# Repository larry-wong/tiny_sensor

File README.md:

基于 ESP32 的家庭智能传感器，搭配 [Home Assistant](https://www.home-assistant.io/) 项目实现家自动化。

小巧的身材上集成温湿度 / 光照度 / 人体存在传感器和红外发射管。

## 硬件设计
* 主控选用 ESP32-S3-WROOM-1
* 温湿度传感器选用 HDC1080
* 光照度传感器选用 GY-302 模块
* 人体存在传感器选用 LD2410B 模块
* 红外发射选用 3mm 发射管
* 状态灯选用贴片发光二极管
* 采用 typec 口供电 / 烧写程序，针脚对应关系：

    | typec | esp32 | 备注 |
    |---|---|---|
    | GND (A1, A12, B1, B12) | GND | 接地 |
    | VBUS (A4, A9, B4, B9) | | 5V |
    | CC1 (A5), CC2 (B5) | GPIO0 | 烧写固件时需接地 |
    | D+ (A6, B6) | GPIO43 | TX |
    | D- (A7, B7) | GPIO44 | RX |

## 电路设计
原理图及 PCB 使用 kicad 绘制，项目文件见 circut 目录（依赖 [ESPRESSIF 官方库](https://github.com/espressif/kicad-libraries)）。

* 所有贴片元件均采用 0805 封装尺寸
* 焊接时可多留一些红外管引脚，以调整发射方向
* 不需要的传感器可留空
* 由于不同颜色发光二极管的压降不同，在 R3 为 100 欧姆时 D2 采用红色发光二极管效果较好，采用黄色发光二极管时亮度较低。若要使用其他颜色发光二极管可自行计算 R3 阻值。

## 固件设计
固件使用 [ESPHome](https://esphome.io/) 搭建，配置文件见 esphome 目录。

* 暴露以下传感器至 Home Assistant:
    * 一个温度传感器
    * 一个湿度传感器
    * 一个光照度传感器
    * 一个人体存在二元传感器
    * 一个人体存在距离传感器
    * 一个可开关的 LED 灯（复用状态灯）
* 项目中对红外管的使用比较客制化，使用自定义的 MQTT 消息驱动。建议改用 [Remote Transmitter](https://esphome.io/components/remote_transmitter.html) 或自行修改。

## 应用参考
接入 Home Assistant 后，可使用暴露出的传感器实现一些家庭自动化，例如：
* 使用人体存在传感器配合光照度传感器控制灯
* 甚至可配合人体存在距离传感器大致确定人体位置后控制不同的灯
* 使用人体存在传感器配合温度传感器控制空调制冷 / 加热 / 关闭
* 使用湿度传感器控制加湿器
* 使用 LED 指示报警信息（电量低，扫地机集尘盒满等）
* 使用红外管控制空调 / 电视 / 浴霸等传统电器
* ……

## 捐赠
如果此项目对你有帮助，可扫描下方二维码请我喝杯咖啡 :)

&nbsp;&nbsp;&nbsp;&nbsp;&nbsp;&nbsp;&nbsp;&nbsp;  &nbsp;&nbsp;&nbsp;&nbsp;&nbsp;&nbsp;&nbsp;&nbsp;&nbsp;&nbsp;&nbsp;&nbsp;&nbsp;&nbsp;&nbsp;&nbsp;

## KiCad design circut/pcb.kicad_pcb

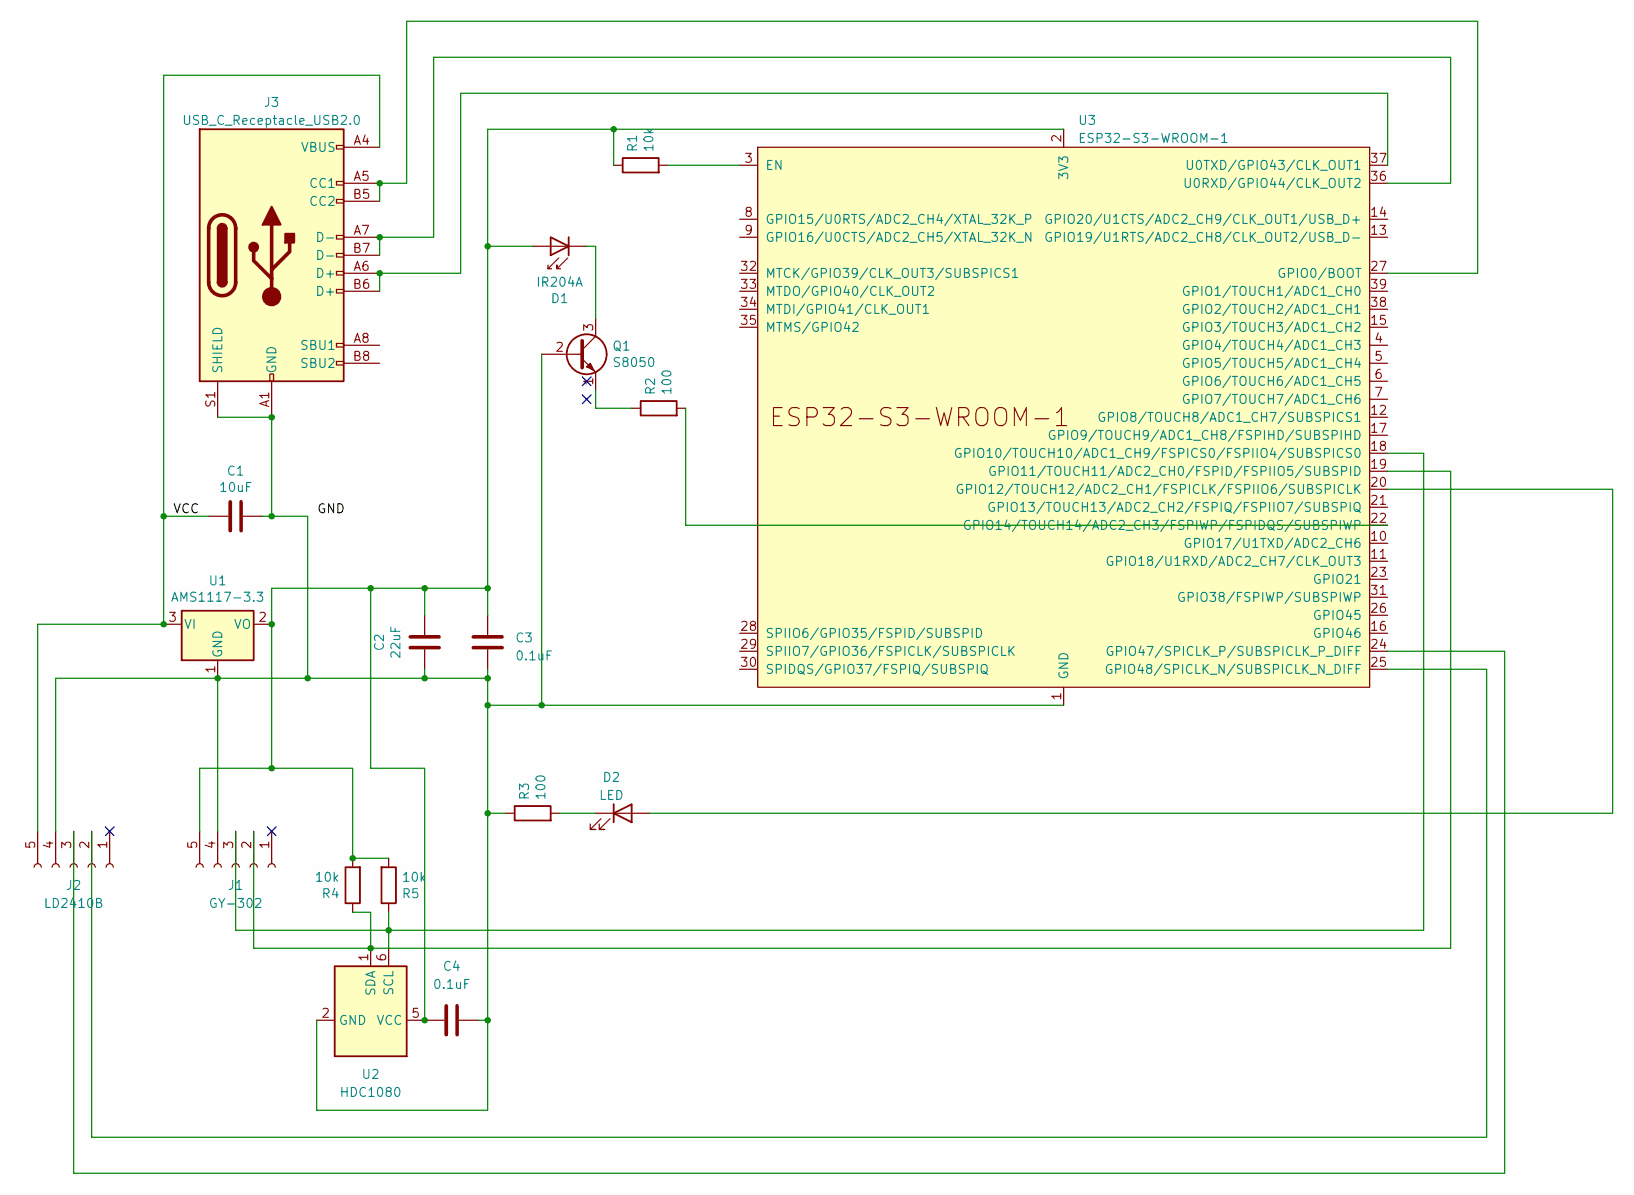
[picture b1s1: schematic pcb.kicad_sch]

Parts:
C1: 10uF; C_0805_2012Metric
C2: 22uF; C_0805_2012Metric
C3, C4: 0.1uF; C_0805_2012Metric
D1: IR204A; LED_D3.0mm_IRBlack
D2: LED; D_0805_2012Metric
J1: GY-302; PinSocket_1x05_P2.54mm_Vertical
J2: LD2410B; PinSocket_1x05_P1.27mm_Vertical
J3: USB_C_Receptacle_USB2.0; USB_C_Receptacle_G-Switch_GT-USB-7010ASV
Q1: S8050; SOT-23
R1, R4, R5: 10k; R_0805_2012Metric
R2, R3: 100; R_0805_2012Metric
U1: AMS1117-3.3; SOT-223-3_TabPin2
U2: HDC1080; Texas_PWSON-N6
U3: ESP32-S3-WROOM-1

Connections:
/VCC: C1.2, J2.5, J3.A4 (VBUS), J3.A9 (VBUS), J3.B4 (VBUS), J3.B9 (VBUS), U1.3 (VI)
unnamed: C2.1, C3.1, C4.1, D1.2 (A), J1.5, R1.1, R4.2, R5.2, U1.2 (VO), U2.5 (VCC), U3.2 (3V3)
unnamed: D1.1 (K), Q1.3 (C)
unnamed: D2.2 (A), U3.20 (GPIO12/TOUCH12/ADC2_CH1/FSPICLK/FSPIIO6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)
unnamed: D2.1 (K), R3.2
unnamed: J1.2, R4.1, U2.1 (SDA), U3.19 (GPIO11/TOUCH11/ADC2_CH0/FSPID/FSPIIO5/S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)
unnamed: J1.3, R5.1, U2.6 (SCL), U3.18 (GPIO10/TOUCH10/ADC1_CH9/FSPICS0/FSPIIO4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)
unnamed: C1.1, C2.2, C3.2, C4.2, J1.4, J2.4, J3.A1 (GND), J3.A12 (GND), J3.B1 (GND), J3.B12 (GND), J3.S1 (SHIELD), Q1.2 (B), R3.1, U1.1 (GND), U2.2 (GND), U3.1 (GND), U3.40 (GND), U3.41 (GND)
unnamed: J2.2, U3.25 (GPIO48/SPICLK_N/SUBSPICLK_N_DIFF)
unnamed: J2.3, U3.24 (GPIO47/SPICLK_P/SUBSPICLK_P_DIFF)
unnamed: J3.A5 (CC1), J3.B5 (CC2), U3.27 (GPIO0/BOOT)
unnamed: Q1.1 (E), R2.1
unnamed: R1.2, U3.3 (EN)
unnamed: R2.2, U3.22 (GPIO14/TOUCH14/ADC2_CH3/FSPIWP/FSPIDQS/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)
unnamed: J3.A7 (D-), J3.B7 (D-), U3.36 (U0RXD/GPIO44/CLK_OUT2)
unnamed: J3.A6 (D+), J3.B6 (D+), U3.37 (U0TXD/GPIO43/CLK_OUT1)

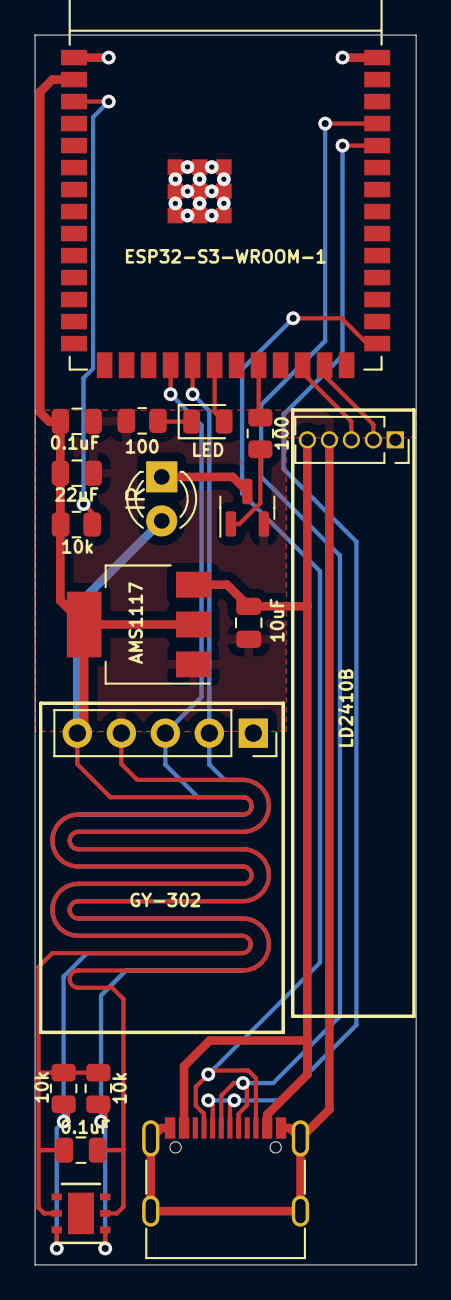
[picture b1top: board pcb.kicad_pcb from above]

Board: 2 copper layers, 22.0 x 71.0 mm, 18 parts (0 on the bottom side), 16 nets.

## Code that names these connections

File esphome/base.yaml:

esphome:
  name: $name
  friendly_name: $friendly_name
  includes:
    - ir_sender.h
  libraries:
    - IRremoteESP8266
  min_version: 2023.12.6

esp32:
  board: esp32-s3-devkitc-1
  framework:
    type: arduino
  variant: esp32s3

# Enable logging
logger:

# Enable Home Assistant API
api:
  encryption:
    key: !secret api_key

ota:
  password: !secret ota_password

wifi:
  ssid: !secret wifi_ssid
  password: !secret wifi_password
  manual_ip:
    static_ip: $ip_addr
    gateway: !secret gateway
    subnet: !secret subnet
  power_save_mode: none
  output_power: 20.5

mqtt:
  broker: !secret mqtt_broker
  port: !secret mqtt_port
  username: !secret mqtt_username
  password: !secret mqtt_password
  discovery: false
  on_message:
    topic: /ir/send/$name
    then:
      - light.turn_on: light_status
      - delay: 0s
      - lambda: |-
          send_ir(&x[0], x.size());
      - light.turn_off: light_status

i2c:
  sda: GPIO11
  scl: GPIO10

uart:
  baud_rate: 256000
  tx_pin: GPIO47
  rx_pin: GPIO48

ld2410:

sensor:
  - platform: bh1750
    name: Immunination
  - platform: hdc1080
    temperature:
      name: Temperature
    humidity:
      name: Humidity
  - platform: ld2410
    detection_distance:
      name: Detection Distance

binary_sensor:
  - platform: ld2410
    has_target:
      name: Presence

switch:
  - platform: ld2410
    bluetooth:
      name: ld2410 Bluetooth

number:
  - platform: ld2410
    timeout:
      name: Presence Timeout
    max_move_distance_gate:
      name: Max Move Distance Gate
    max_still_distance_gate:
      name: Max Still Distance Gate
    g0:
      move_threshold:
        name: g0 Move Threshold
      still_threshold:
        name: g0 Still Threshold
    g1:
      move_threshold:
        name: g1 Move Threshold
      still_threshold:
        name: g1 Still Threshold
    g2:
      move_threshold:
        name: g2 Move Threshold
      still_threshold:
        name: g2 Still Threshold
    g3:
      move_threshold:
        name: g3 Move Threshold
      still_threshold:
        name: g3 Still Threshold
    g4:
      move_threshold:
        name: g4 Move Threshold
      still_threshold:
        name: g4 Still Threshold
    g5:
      move_threshold:
        name: g5 Move Threshold
      still_threshold:
        name: g5 Still Threshold
    g6:
      move_threshold:
        name: g6 Move Threshold
      still_threshold:
        name: g6 Still Threshold
    g7:
      move_threshold:
        name: g7 Move Threshold
      still_threshold:
        name: g7 Still Threshold
    g8:
      move_threshold:
        name: g8 Move Threshold
      still_threshold:
        name: g8 Still Threshold

light:
  - platform: status_led
    id: light_status
    name: Status
    pin: GPIO12
    icon: "mdi:led-outline"

custom_component:
  - lambda: |-
      auto ir_sender = new IRSender();
      return {ir_sender};

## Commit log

2024-01-16 optimize pcb layout
